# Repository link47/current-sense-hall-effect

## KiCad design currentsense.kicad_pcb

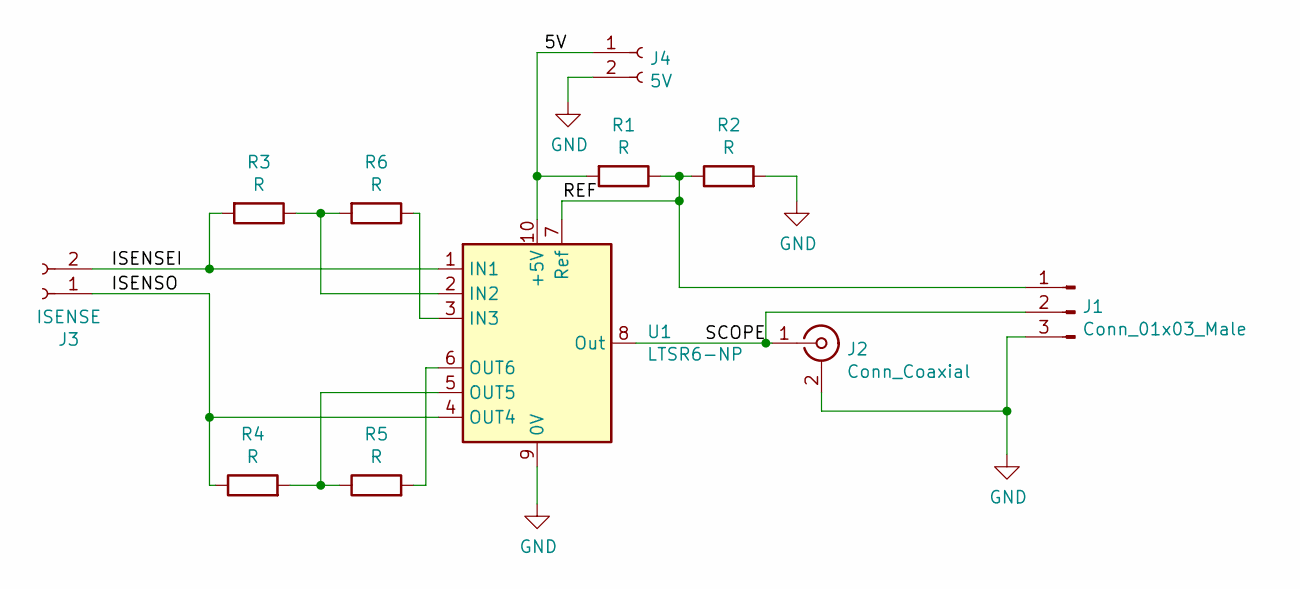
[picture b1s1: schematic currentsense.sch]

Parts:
J1: Conn_01x03_Male; PinHeader_1x03_P2.54mm_Vertical
J2: Conn_Coaxial; 5227161-1
J3: ISENSE; TerminalBlock_Phoenix_MKDS-1,5-2_1x02_P5.00mm_Horizontal
J4: 5V; TerminalBlock_Phoenix_MKDS-1,5-2_1x02_P5.00mm_Horizontal
R1, R2, R3, R4, R5, R6: R; R_0805_2012Metric_Pad1.15x1.40mm_HandSolder
U1: LTSR6-NP; LEM_LTSR-NP

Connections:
/5V: J4.1, R1.2, U1.10 (+5V)
/ISENSEI: J3.2, R3.2, U1.1 (IN1)
/ISENSO: J3.1, R4.1, U1.4 (OUT4)
/REF: J1.1, R1.1, R2.1, U1.7 (Ref)
/SCOPE: J1.2, J2.1 (In), U1.8 (Out)
GND: J1.3, J2.2 (Ext), J4.2, R2.2, U1.9 (0V)
unnamed: R3.1, R6.2, U1.2 (IN2)
unnamed: R4.2, R5.1, U1.5 (OUT5)
unnamed: R5.2, U1.6 (OUT6)
unnamed: R6.1, U1.3 (IN3)

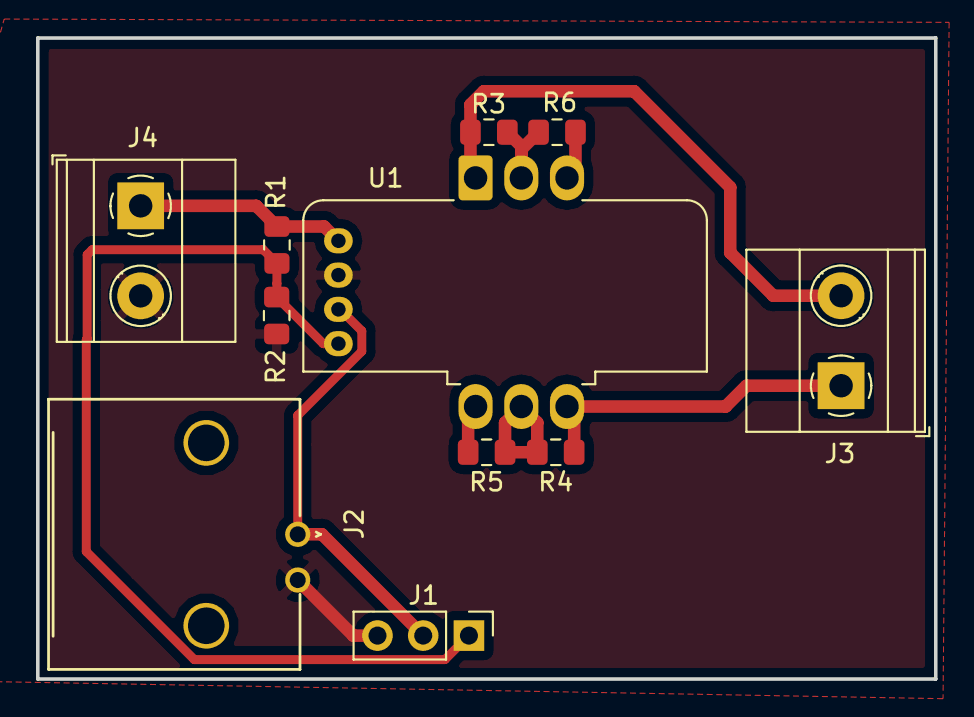
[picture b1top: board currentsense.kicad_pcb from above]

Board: 2 copper layers, 49.9 x 35.6 mm, 11 parts (0 on the bottom side), 10 nets.

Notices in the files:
parts and their libraries:
Copyright 2016 Accelerated Designs. All rights reserved.
